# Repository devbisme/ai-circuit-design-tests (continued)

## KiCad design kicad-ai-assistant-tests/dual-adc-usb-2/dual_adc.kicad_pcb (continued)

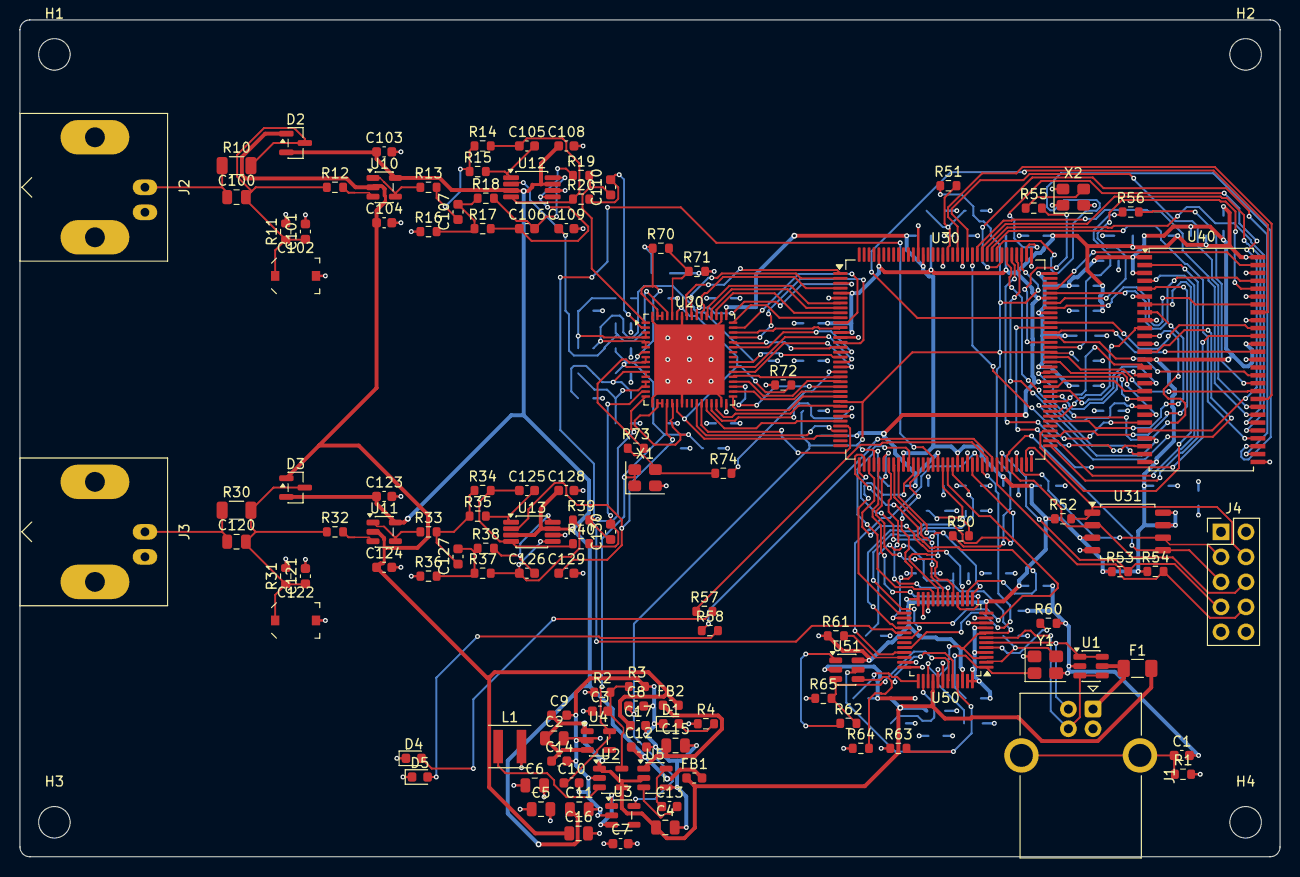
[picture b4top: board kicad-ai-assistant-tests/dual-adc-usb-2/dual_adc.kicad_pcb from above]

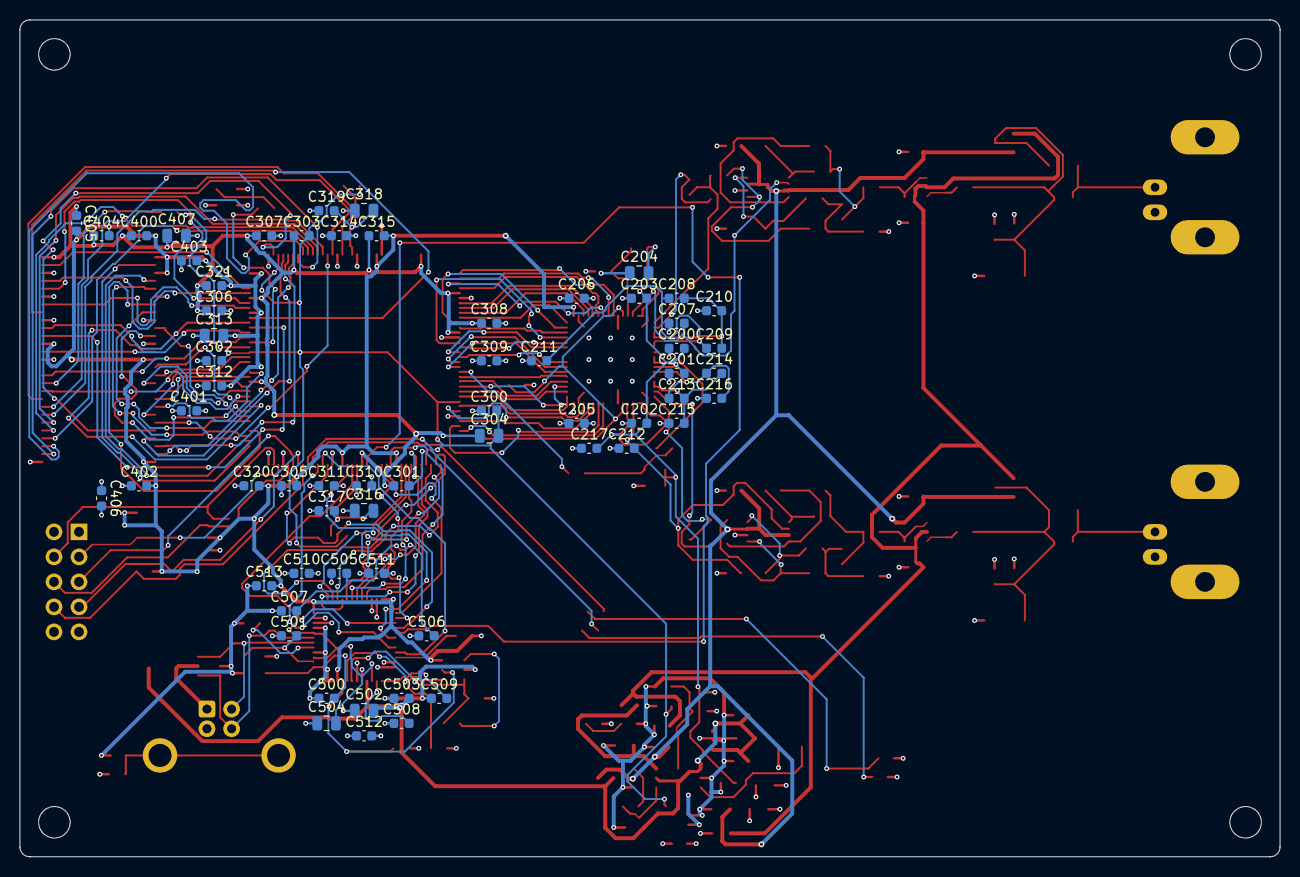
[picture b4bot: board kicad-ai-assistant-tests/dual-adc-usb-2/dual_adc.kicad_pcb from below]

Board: 4 copper layers, 128.0 x 85.0 mm, 182 parts (62 on the bottom side), 160 nets.

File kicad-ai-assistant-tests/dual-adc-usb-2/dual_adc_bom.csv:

Qty,Value,Footprint,References,Description
1,4.7n,Capacitor_SMD:C_0603_1608Metric,C1,shield RF tie (250 V)
6,4.7u,Capacitor_SMD:C_0805_2012Metric,C2 C4 C15 C16 C502 C504,+5V bulk (keep total VBUS C ~10 uF)
1,22p,Capacitor_SMD:C_0603_1608Metric,C3,FB feed-forward
2,22u,Capacitor_SMD:C_0805_2012Metric,C5 C6,buck output
6,1u,Capacitor_SMD:C_0603_1608Metric,C7 C8 C9 C10 C13 C14,LDO in
7,10u,Capacitor_SMD:C_0805_2012Metric,C11 C204 C304 C313 C316 C318 C407,
58,100n,Capacitor_SMD:C_0603_1608Metric,C12 C17 C103 C104 C108 C109 C123 C124 C128 C129 C200 C201 C202 C203 C205 C206 C209 C210 C211 C214 C215 C216 C217 C300 C301 C302 C303 C305 C306 C307 C308 C309 C310 C311 C312 C314 C315 C317 C319 C320 C321 C400 C401 C402 C403 C404 C405 C406 C503 C505 C506 C507 C508 C509 C510 C511 C512 C513,
2,15p C0G 100V,Capacitor_SMD:C_0805_2012Metric,C100 C120,attenuator top comp
2,120p C0G,Capacitor_SMD:C_0603_1608Metric,C101 C121,attenuator bottom comp
2,5-30p,Capacitor_SMD:C_Trimmer_Murata_TZC3,C102 C122,compensation trim (adjust for flat 1 kHz square wave)
4,47p C0G,Capacitor_SMD:C_0603_1608Metric,C105 C106 C125 C126,MFB C2 (signal leg)
2,220p C0G,Capacitor_SMD:C_0603_1608Metric,C107 C127,MFB C1 (differential)
2,470p C0G,Capacitor_SMD:C_0603_1608Metric,C110 C130,"differential RC pole, ~3.4 MHz"
4,2.2u,Capacitor_SMD:C_0603_1608Metric,C207 C208 C212 C213,VCM bypass
2,18p,Capacitor_SMD:C_0603_1608Metric,C500 C501,crystal load
2,green,LED_SMD:LED_0603_1608Metric,D1 D4,power LED
2,BAV99,Package_TO_SOT_SMD:SOT-23,D2 D3,input clamp to analog rails
1,yellow,LED_SMD:LED_0603_1608Metric,D5,status LED 2
1,0.5A hold,Fuse:Fuse_1206_3216Metric,F1,"resettable fuse, 500 mA hold"
2,BLM18PG221,Inductor_SMD:L_0603_1608Metric,FB1 FB2,analog +5 V filter
1,USB-B,Connector_USB:USB_B_OST_USB-B1HSxx_Horizontal,J1,USB 2.0 type-B receptacle
2,BNC,Connector_Coaxial:BNC_Amphenol_B6252HB-NPP3G-50_Horizontal,J2 J3,channel A input (scope-probe compatible)
1,PROG,Connector_PinHeader_2.54mm:PinHeader_2x05_P2.54mm_Vertical,J4,SPI flash programming header (iceprog-style)
1,2.2u XFL4020-222,Inductor_SMD:L_Coilcraft_XxL4020,L1,buck inductor
1,1M,Resistor_SMD:R_0603_1608Metric,R1,shield bleed
1,453k,Resistor_SMD:R_0603_1608Metric,R2,FB top: Vout = 0.6*(1+453k/100k) = 3.32 V
1,100k,Resistor_SMD:R_0603_1608Metric,R3,FB bottom
5,1k,Resistor_SMD:R_0603_1608Metric,R4 R12 R32 R57 R58,
2,909k 0.1%,Resistor_SMD:R_1206_3216Metric,R10 R30,attenuator top
2,100k 0.1%,Resistor_SMD:R_0603_1608Metric,R11 R31,attenuator bottom
4,806,Resistor_SMD:R_0603_1608Metric,R13 R16 R33 R36,MFB R1 (signal leg)
4,768,Resistor_SMD:R_0603_1608Metric,R14 R17 R34 R37,MFB R2 (signal leg)
4,147,Resistor_SMD:R_0603_1608Metric,R15 R18 R35 R38,MFB R3 (signal leg)
4,49.9,Resistor_SMD:R_0603_1608Metric,R19 R20 R39 R40,ADC drive / RC pole
2,100,Resistor_SMD:R_0603_1608Metric,R50 R51,PLL supply filter
9,10k,Resistor_SMD:R_0603_1608Metric,R52 R53 R54 R61 R63 R64 R65 R71 R72,SS_B high at reset -> SPI master boot
3,33,Resistor_SMD:R_0603_1608Metric,R55 R73 R74,
1,22,Resistor_SMD:R_0603_1608Metric,R56,SDRAM clock series term
1,12k 1%,Resistor_SMD:R_0603_1608Metric,R60,FT232H PHY reference
1,2.2k,Resistor_SMD:R_0603_1608Metric,R62,EEPROM DO -> EEDATA
1,20k,Resistor_SMD:R_0603_1608Metric,R70,"MODE = VDD/3: offset binary, DCS on"
1,USBLC6-2SC6,Package_TO_SOT_SMD:SOT-23-6,U1,USB ESD protection
1,TLV62569DBV,Package_TO_SOT_SMD:SOT-23-5,U2,5V->3.3V 2 A buck
1,TLV73312PDBV,Package_TO_SOT_SMD:SOT-23-5,U3,FPGA core 1.2 V LDO
1,LP5907MFX-3.3,Package_TO_SOT_SMD:SOT-23-5,U4,low-noise ADC supply
1,TPS60403DBV,Package_TO_SOT_SMD:SOT-23-5,U5,"inverting charge pump, 60 mA"
2,OPA810IDBVR,Package_TO_SOT_SMD:SOT-23-5,U10 U11,FET-input unity-gain buffer
2,THS4521IDGK,Package_SO:VSSOP-8_3x3mm_P0.65mm,U12 U13,fully-differential ADC driver / 2-pole MFB
1,LTC2290CUP,Package_DFN_QFN:QFN-64-1EP_9x9mm_P0.5mm_EP7.15x7.15mm,U20,dual 12-bit 10 Msps ADC
1,ICE40HX4K-TQ144,Package_QFP:TQFP-144_20x20mm_P0.5mm,U30,"FPGA: capture, SDRAM, USB FIFO"
1,W25Q32JVSSIQ,Package_SO:SOIC-8_5.3x5.3mm_P1.27mm,U31,FPGA configuration flash (32 Mbit)
1,MT48LC16M16A2P-6A,Package_SO:TSOP-II-54_22.2x10.16mm_P0.8mm,U40,256 Mbit SDR SDRAM capture buffer
1,FT232HL,Package_QFP:LQFP-48_7x7mm_P0.5mm,U50,USB 2.0 HS to sync FIFO bridge
1,93LC56BT-I/OT,Package_TO_SOT_SMD:SOT-23-6,U51,FT232H config EEPROM (sets 245 sync FIFO mode)
1,ASE-10.000MHZ,Oscillator:Oscillator_SMD_Abracon_ASE-4Pin_3.2x2.5mm,X1,"10 MHz sample clock (dedicated, low jitter)"
1,ASE-50.000MHZ,Oscillator:Oscillator_SMD_Abracon_ASE-4Pin_3.2x2.5mm,X2,50 MHz system clock
1,12MHz 10pF,Crystal:Crystal_SMD_3225-4Pin_3.2x2.5mm,Y1,FT232H crystal

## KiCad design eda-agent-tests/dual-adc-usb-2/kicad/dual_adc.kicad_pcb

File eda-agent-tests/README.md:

# eda-agent — tests

## Tool under test

[eda-agent](https://github.com/salitronic/eda-agent) is an MCP server with three backends:
Altium Designer (the default and most complete, Windows only), KiCad, and EasyEDA Pro. These
tests used the **KiCad backend**, which exposes 109 tools (`mcp__eda-kicad__*`) for:

- Design creation from a JSON **DesignPlan** written by the LLM: `design_validate_plan`,
  `design_review_plan`, and `kicad_generate_project`, which writes `.kicad_pro`,
  `.kicad_sch` and `.kicad_pcb` from the plan.
- Review: `kicad_full_review` (ERC + DRC + schematic review + schematic/PCB compare),
  `kicad_review_schematic`, `kicad_compare_sch_pcb`.
- Board queries and simple edits (tracks, vias, zones, moves) over KiCad's IPC API.
- Exports (Gerbers, drill, BOM, STEP, renders, …), SPICE, and PCB calculators.

Nearly every KiCad tool needs the KiCad GUI open with its IPC API server enabled. The
`kicad_generate_*` tools write files directly. The autonomous spec-to-board harness
(`autodesign` skill) exists only for Altium and EasyEDA, so it was not installed.
Installation is described in [`setup.md`](setup.md).

The tool is a hybrid (both analyzer and generator), so it is tested in both roles, like
[kicad-mcp-server](../kicad-mcp-server-tests/) and [kicad-mcp-pro](../kicad-mcp-pro-tests/).

- **Version:** eda-agent 0.6.1 (Alpha), commit 8e659a2 (2026-10-07), installed from `main`.
- **Toolset:** full (not `EDA_AGENT_TOOLSET=minimal`), headless (no web dashboard).
- **Model:** Claude Opus 5.5 on a Claude Pro plan, Claude Code v2.1.296 (both runs).
- **Backend:** KiCad 10.0.4 (`~/bin/kicad10-root`, IPC API and bundled Python 3.11),
  Freerouting 2.4.1.

## Runs

| Run | What it tests | Prompts | Outcome | Equiv. API cost | Time |
|---|---|---|---|---|---|
| [`dual-adc-usb-1`](dual-adc-usb-1/) | **Analysis** and fab outputs for an existing design | 1 (`analysis_prompt.txt`) | ERC/DRC 0 errors; 19 ranked issues; Gerbers, BOM, CPL, PNG | $3.43 | ~14 min |
| [`dual-adc-usb-2`](dual-adc-usb-2/) | A **full design**, from requirements to Gerbers | 1, plus 1 for the summary | 7-sheet schematic, routed 4-layer board, ERC and DRC 0 errors | $18.47 | ~1h56m wall clock, ~47 min working |

Each run directory has an `executive_summary.md`; start there. Costs are the equivalent
first-party API price of the tokens used (`claude_cost.txt`), not what the Pro subscription
billed. Run 2's `claude_cost.txt` was generated after the session ended, from that session's
transcripts; it includes the summary prompt. I have not yet validated the findings in either
run myself.

### dual-adc-usb-1: analyzer on an existing design

The input is the KiCad project produced by
[Konnect run 2](../konnect-tests/dual-adc-usb-2/): a 4-layer, 140 × 90 mm dual-channel
12-bit, 10 MS/s ADC board with a USB 2.0 interface (LTC2290 ADC, iCE40HX4K FPGA, SDRAM,
FT2232HL). The KiCad files are unchanged copies of Konnect's (the `.kicad_pcb` md5 matches),
and this run did not modify them. kicad-happy, kicad-mcp-server and kicad-mcp-pro run 1
analyzed the same design.

Prompt (from `claude_transcript.txt`):

```
execute the instructions in analysis_prompt.txt.
```

[`analysis_prompt.txt`](dual-adc-usb-1/analysis_prompt.txt) asks for an architectural,
physical-design and manufacturing review **using eda-agent**, JLCPCB Gerbers, BOM and
pick-and-place files, a dark-gray PCB PNG, and `executive_summary.md`.

This run replaces an earlier run 1 whose prompt didn't name eda-agent; in that one Claude
used only `kicad-cli` and pcbnew Python and made no `eda-kicad` calls. The only change to
the prompt is the words "using eda-agent".

Quick look:

- **Connecting to KiCad:** the dual-adc-usb-2 session's pcbnew held `/tmp/kicad/api.sock`,
  so Claude started a second pcbnew on this board, which took over the socket, and pointed
  the socket back at the other instance afterwards.
- **eda-agent tools used:** `kicad_full_review`; board queries (summary, stackup, fab stats,
  vias, zones, layer usage, trace lengths, diff pairs, net classes, tracks, pads); the
  impedance calculators; `kicad_export_netlist`, `kicad_export_gerbers`, `kicad_export_drill`,
  `kicad_export_bom`, `kicad_export_pos`; and the `kicad_cli` passthrough.
- **Checks:** ERC 0 errors, 203 warnings (201 are missing-library warnings from the
  kicad-cli environment, so ERC's library-mismatch check didn't run). DRC 0 errors,
  0 unconnected, 343 cosmetic or library warnings. Parity: 174 warnings, all `Datasheet`
  field noise or the mounting holes.
- All 34 embedded symbols match the stock KiCad library pin-for-pin. The BAV199DW clamp
  wiring was confirmed against the Diodes datasheet, despite misleading KiCad pin names.
- 19 ranked issues. The most serious:
  - The FPGA's 10 MHz clock runs from the gated analog rail, so there is no clock until USB
    enumerates, and the unpowered ADC may be back-powered by the FPGA.
  - ADC inputs can be driven past absolute maximum by large BNC voltages.
  - Decoupling caps sit 5–22 mm from their pins (14 of 16 FPGA supply pins over 5 mm), and
    the anti-alias caps are 16–18 mm from the ADC.
  - LM27762 feedback resistors (49.9 kΩ) are below the datasheet's 50 kΩ minimum, and its
    unused PGOOD is left open instead of grounded.
  - 40 MB/s is at or above the FT2232H sync-FIFO limit; 16 MB SDRAM gives only ~0.4 s.
- JLCPCB Gerber zip, BOM (blank LCSC column), CPL and a 400 dpi PNG were produced.
- Only the LM27762 and BAV199DW datasheets could be downloaded (FTDI returned 403;
  analog.com timed out). Findings that rest on the FT2232H, LTC2290 and ADA4817 are from the
  model's memory, and the summary marks them.

eda-agent gaps that Claude worked around:

- Every query needs a running KiCad, and the server connects only to `/tmp/kicad/api.sock`.
- `kicad_full_review` truncates ERC and DRC to 200 rows each, so they were rerun in full
  through `kicad_cli`. Its schematic and PCB findings were 53 deliberate single-pin
  no-connect nets, and its decoupling check tests only that caps exist, not their distance.
- `kicad_list_pads` omits component references, so the per-IC geometry (decoupling distances,
  per-net routing) was done with KiCad's bundled pcbnew Python, read-only
  (`reports/scripts/pcb_an.py`).
- The exports aren't fab-ready: Gerbers include all 20 layers, the BOM is one ungrouped row
  per part, and the position file is ASCII in inches. Claude zipped only the fab layers,
  regenerated positions as mm CSV via `kicad_cli`, and converted both to JLC format by
  script. The PNG came from an SVG plotted through `kicad_cli`.

### dual-adc-usb-2: full design

The prompt is [`dual-adc-prompt.txt`](dual-adc-usb-2/dual-adc-prompt.txt). It is identical
to the one used for Konnect run 2, kicad-mcp-server run 2, kicad-happy run 2 and
kicad-mcp-pro run 2.

Prompts, in sequence in one session, with no other user intervention:

```
create the design described in dual-adc-prompt.txt.
```
```
write the executive_summary.md for this run
```

Quick look:

- **Design:** BNC → 1 MΩ compensated ÷11 divider → BAV99 clamp → OPA1656 buffer → THS4521
  FDA → LTC2290; iCE40HX4K with 32 MB SDRAM (0.8 s capture); FT232H sync FIFO; USB-B, bus
  powered (~330 mA estimated). Decisions with options are in
  [`design_decisions.md`](dual-adc-usb-2/design_decisions.md).
- **Schematic:** 7 sheets, 179 parts, 185 nets, ERC 0 errors. The netlist matches the
  DesignPlan net-for-net.
- **PCB:** 125 × 95 mm, 4 layers (In1 GND, In2 +3V3 with a +3V3A island). DRC 0 errors,
  0 unconnected, 0 parity issues, 19 silkscreen warnings. `kicad_full_review` 0 errors.
- **How the server was used:** as a **design tool** for plan validation and review, project
  generation, and the final review and exports. The ~50 kB DesignPlan went through
  `scripts/mcp_call.py`, which calls the tool functions in-process.
- **What it contributed:** the plan validator caught real errors, and the generated board
  had every pad on the right net (725/725), so it became the starting board.
- **Server bugs and gaps:**
  - The generated schematic has no connectivity: its global labels touch no pins (780 ERC
    violations, empty netlist), and multi-unit parts get only unit 1.
  - Symbol and footprint lookup needs a running KiCad, silently falls back to box symbols
    without one, and can't read KiCad 10 `.kicad_symdir` libraries.
  - The generated board is 2-layer with grid placement, FPIDs without library nicknames, and
    no symbol links.
  - No placement, routing, zone or DSN/SES tools on KiCad.
  - `design_review_plan` misidentifies circuits (calls the compensated divider an RC
    high-pass and low-pass).
  - The IPC tools only try `/tmp/kicad/api.sock`; a stale socket blocked them until it was
    relinked.
- **Gaps filled by Claude's own scripts:** a label-based schematic writer, 4-layer
  conversion and placement, plane fanout and DSN, 4 Freerouting runs, a small A* router and
  local re-layout around the LM27762 (all in `scripts/`).
- **Not ready for fab:** the FT232H and LTC2290 support circuits weren't checked against
  datasheets (both downloads failed); input compensation caps are estimates; first-order
  anti-alias filter; no USB pre-enumeration current limit; no SDRAM/FIFO length matching;
  no gateware or host software.

## Layout

```
eda-agent-tests/
├── README.md                   <- this file
├── setup.md                    <- how eda-agent was installed and configured
├── dual-adc-usb-1/             <- run 1: analysis of the Konnect run-2 design
│   ├── executive_summary.md    <- start here
│   ├── analysis_prompt.txt     <- the analysis prompt
│   ├── claude_transcript.txt   <- session transcript (/export)
│   ├── claude_cost.txt         <- token usage and equivalent API cost
│   ├── session_cost.py         <- script that produced claude_cost.txt
│   ├── dual_adc_usb.kicad_pro, .kicad_pcb, .kicad_dru, .kicad_prl, .kicad_sch
│   ├── afe_a, afe_b, adc, fpga, usb, power .kicad_sch
│   ├── reports/                <- drc.json, erc.json, eda_agent_full_review.json, netlist,
│   │                              raw eda-agent BOM/positions, pcb_geometry.txt, scripts/
│   ├── jlcpcb/                 <- Gerber zip, gerbers/, assembly/ (BOM and CPL)
│   └── dual_adc_usb_pcb.png    <- PCB image on a dark-gray background
└── dual-adc-usb-2/             <- run 2: full design from the dual-ADC prompt
    ├── executive_summary.md    <- start here
    ├── README.md               <- run details, eda-agent findings, regeneration steps
    ├── design_decisions.md     <- requirements, derived numbers, decisions with options
    ├── dual-adc-prompt.txt     <- the design prompt
    ├── claude_transcript.txt   <- session transcript (/export)
    ├── claude_cost.txt         <- token usage and equivalent API cost
    ├── session_cost.py         <- script that produced claude_cost.txt
    ├── plan/                   <- DesignPlan (full and compact), review output, no-connects
    ├── eda_agent_raw/          <- the project as kicad_generate_project wrote it
    ├── kicad/                  <- the final KiCad project
    │   ├── dual_adc.kicad_pro, .kicad_sch, .kicad_pcb, .kicad_prl
    │   ├── power, usb, frontend, adc, fpga, memory .kicad_sch
    │   ├── erc.rpt, drc.rpt, dual_adc.net, dual_adc_bom.csv
    │   ├── dual_adc_schematic.pdf, dual_adc_pcb_top.pdf, dual_adc.png (3D render)
    │   └── fab/                <- Gerbers, drill and positions
    ├── route/                  <- placed/prerouted/routed boards, DSN, SES, Freerouting logs
    └── scripts/                <- workarounds for server gaps
        ├── build_plan.py       <- writes the DesignPlan (single source of truth)
        ├── check_pins.py       <- pin coverage check of the plan
        ├── symlib.py           <- reads KiCad 10 .kicad_symdir libraries
        ├── sch_writer.py       <- label-based schematic writer
        ├── mcp_call.py         <- calls eda-agent tools in-process
        ├── build_pcb.py        <- 4 layers, FPIDs, symbol links, placement
        ├── board_sync.py       <- relinks the board to new schematic UUIDs
        ├── route_prep.py       <- plane fanout and DSN for Freerouting
        ├── post_route.py       <- imports the SES
        ├── fix_unrouted.py     <- grid A* router for leftover connections
        ├── surgery_lm27762*.py <- one-off local re-layout around the LM27762
        ├── cleanup_board.py    <- final board cleanup
        ├── patch_project.py    <- net classes (pcbnew Save rewrites .kicad_pro)
        └── check_pcb_nets.py, compare_netlist.py, plot_area.py, plot_draw.py
```

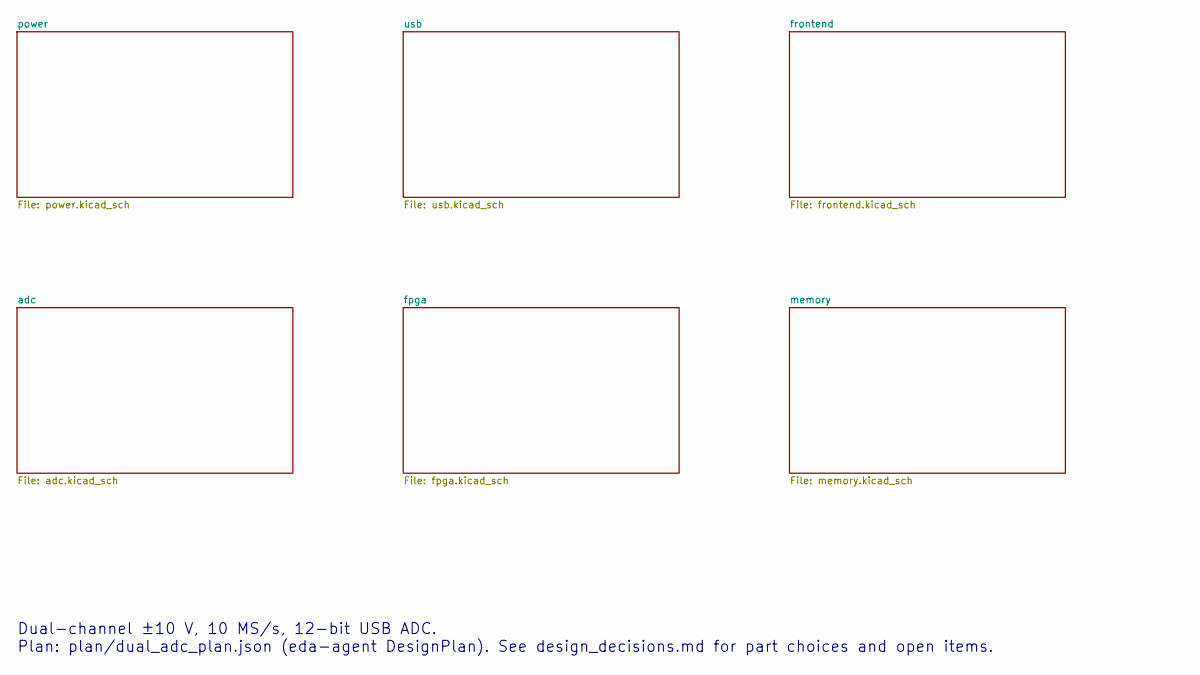
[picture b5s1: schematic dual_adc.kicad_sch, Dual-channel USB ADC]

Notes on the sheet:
Dual-channel ±10 V, 10 MS/s, 12-bit USB ADC. Plan: plan/dual_adc_plan.json (eda-agent DesignPlan). See design_decisions.md for part choices and open items.

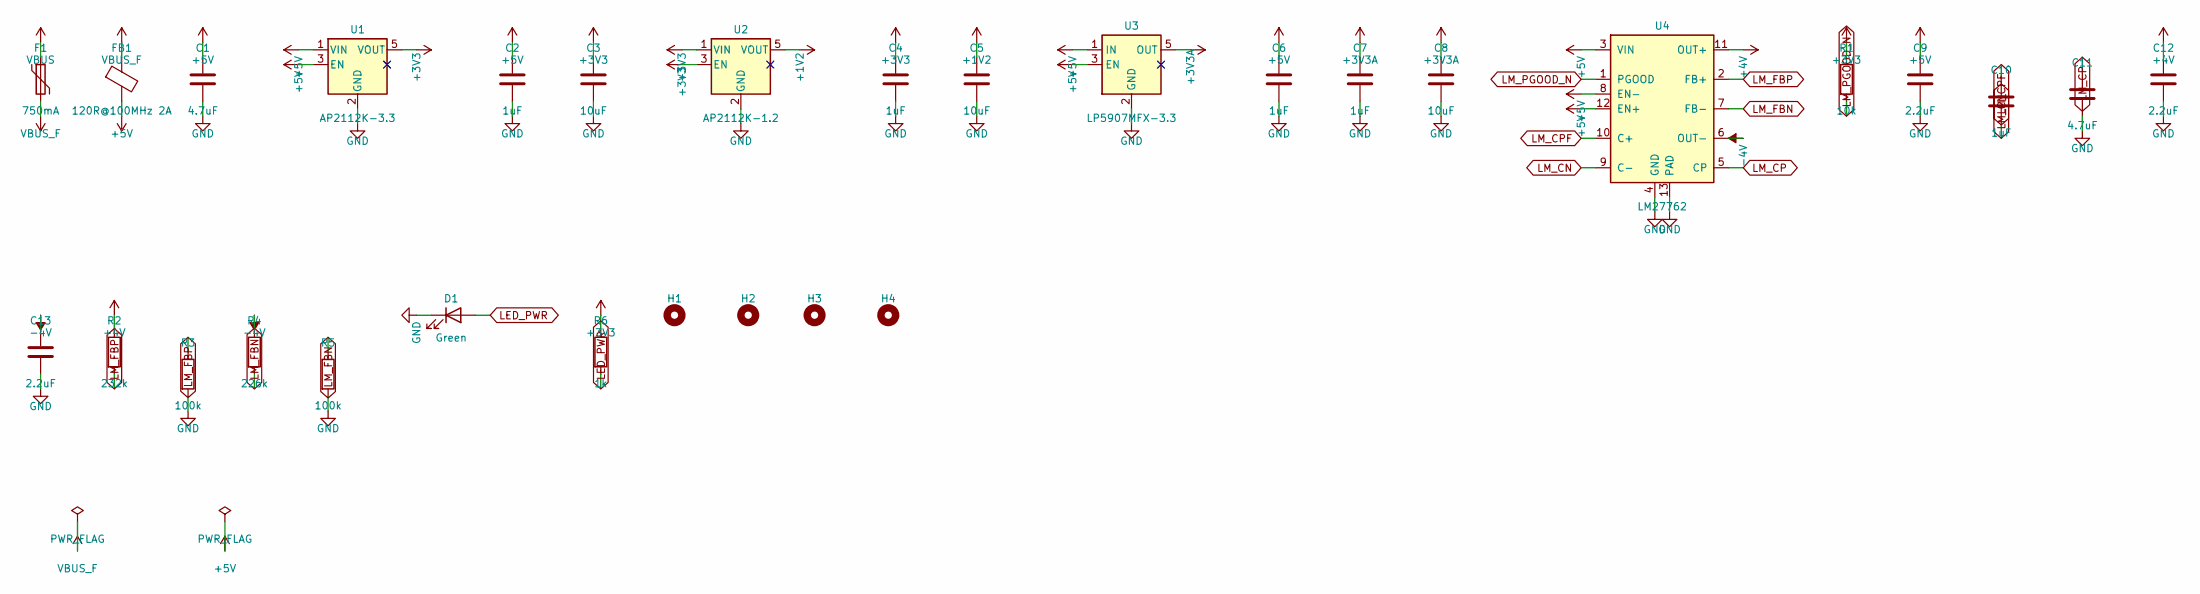
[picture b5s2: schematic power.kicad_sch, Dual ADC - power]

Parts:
C1, C11: 4.7uF; C_0805_2012Metric
C2, C4, C6, C7: 1uF; C_0603_1608Metric
C3, C5, C8: 10uF; C_0805_2012Metric
C9, C12, C13: 2.2uF; C_0805_2012Metric
C10: 1uF; C_0402_1005Metric
D1: Green; LED_0603_1608Metric
F1: 750mA; Fuse_1206_3216Metric; MPN 0ZCJ0050AF2E
FB1: 120R@100MHz 2A; L_0603_1608Metric; MPN BLM18AG601SN1D
H1, H2, H3, H4: MountingHole; MountingHole_3.2mm_M3
R1: 10k; R_0603_1608Metric
R2: 232k; R_0603_1608Metric
R3, R5: 100k; R_0603_1608Metric
R4: 226k; R_0603_1608Metric
R6: 1k; R_0603_1608Metric
U1: AP2112K-3.3; SOT-23-5; MPN AP2112K-3.3TRG1
U2: AP2112K-1.2; SOT-23-5; MPN AP2112K-1.2TRG1
U3: LP5907MFX-3.3; SOT-23-5; MPN LP5907MFX-3.3/NOPB
U4: LM27762; WSON-12-1EP_3x2mm_P0.5mm_EP1x2.65; MPN LM27762DSSR

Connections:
+1V2: C5.1, U2.5 (VOUT); also elsewhere on the board
+3V3: C3.1, C4.1, R1.1, R6.1, U1.5 (VOUT), U2.1 (VIN), U2.3 (EN); also elsewhere on the board
+3V3A: C7.1, C8.1, U3.5 (OUT); also elsewhere on the board
+4V: C12.1, R2.1, U4.11 (OUT+); also elsewhere on the board
+5V: C1.1, C2.1, C6.1, C9.1, FB1.2, U1.1 (VIN), U1.3 (EN), U3.1 (IN), U3.3 (EN), U4.3 (VIN), U4.8 (EN-), U4.12 (EN+)
-4V: C13.1, R4.1, U4.6 (OUT-); also elsewhere on the board
GND: C1.2, C2.2, C3.2, C4.2, C5.2, C6.2, C7.2, C8.2, C9.2, C11.2, C12.2, C13.2, D1.1 (K), R3.2, R5.2, U1.2 (GND), U2.2 (GND), U3.2 (GND), U4.4 (GND), U4.13 (PAD); also elsewhere on the board
LED_PWR: D1.2 (A), R6.2
LM_CN: C10.2, U4.9 (C-)
LM_CP: C11.1, U4.5 (CP)
LM_CPF: C10.1, U4.10 (C+)
LM_FBN: R4.2, R5.1, U4.7 (FB-)
LM_FBP: R2.2, R3.1, U4.2 (FB+)
LM_PGOOD_N: R1.2, U4.1 (PGOOD); also elsewhere on the board
VBUS: F1.1; also elsewhere on the board
VBUS_F: F1.2, FB1.1; also elsewhere on the board

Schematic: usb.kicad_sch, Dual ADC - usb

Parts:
C14: 4.7nF; C_0603_1608Metric
C15, C19, C20, C21, C22, C23, C24, C26, C27, C28: 100nF; C_0603_1608Metric
C16, C17: 27pF; C_0603_1608Metric
C18, C25: 4.7uF; C_0805_2012Metric
FB2: 600R@100MHz; L_0603_1608Metric; MPN BLM18AG601SN1D
J1: USB_B; USB_B_OST_USB-B1HSxx_Horizontal; MPN USB-B1HSW6
R7: 1M; R_0603_1608Metric
R8: 12k; R_0603_1608Metric; Tolerance 1%
R9, R10, R12, R13, R14: 10k; R_0603_1608Metric
R11: 2.2k; R_0603_1608Metric
U5: USBLC6-2SC6; SOT-23-6; MPN USBLC6-2SC6
U6: FT232HL; LQFP-48_7x7mm_P0.5mm; MPN FT232HL-REEL
U7: 93LC56B; SOIC-8_3.9x4.9mm_P1.27mm; MPN 93LC56BT-I/SN
Y1: 12MHz; Crystal_SMD_3225-4Pin_3.2x2.5mm; MPN ABM8-12.000MHZ-B2-T

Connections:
+3V3: C21.1, C22.1, C23.1, C24.1, C25.1, C28.1, FB2.1, R9.1, R10.1, R12.1, R13.1, R14.1, U6.12 (VCCIO), U6.24 (VCCIO), U6.39 (VCCD), U6.40 (VREGIN), U6.46 (VCCIO), U7.8 (VCC); also elsewhere on the board
FT_ACBUS8: U6.32 (ACBUS8); also elsewhere on the board
FT_ACBUS9: U6.33 (ACBUS9); also elsewhere on the board
FT_CLKOUT: U6.29 (ACBUS5); also elsewhere on the board
FT_D0: U6.13 (ADBUS0); also elsewhere on the board
FT_D1: U6.14 (ADBUS1); also elsewhere on the board
FT_D2: U6.15 (ADBUS2); also elsewhere on the board
FT_D3: U6.16 (ADBUS3); also elsewhere on the board
FT_D4: U6.17 (ADBUS4); also elsewhere on the board
FT_D5: U6.18 (ADBUS5); also elsewhere on the board
FT_D6: U6.19 (ADBUS6); also elsewhere on the board
FT_D7: U6.20 (ADBUS7); also elsewhere on the board
FT_EECLK: R13.2, U6.44 (EECLK), U7.2 (SCLK)
FT_EECS: R12.2, U6.45 (EECS), U7.1 (CS)
FT_EEDATA: R11.2, R14.2, U6.43 (EEDATA), U7.3 (DI)
FT_EEDO: R11.1, U7.4 (DO)
FT_OE_N: U6.30 (ACBUS6); also elsewhere on the board
FT_PWRSAV_N: R9.2, U6.31 (ACBUS7)
FT_RD_N: U6.26 (ACBUS2); also elsewhere on the board
FT_REF: R8.1, U6.5 (REF)
FT_RESET_N: R10.2, U6.34 (~RESET)
FT_RXF_N: U6.21 (ACBUS0); also elsewhere on the board
FT_SIWU_N: U6.28 (ACBUS4); also elsewhere on the board
FT_TXE_N: U6.25 (ACBUS1); also elsewhere on the board
FT_VCCA: C26.1, U6.37 (VCCA)
FT_VCORE: C27.1, U6.38 (VCCCORE)
FT_VPHY: C18.1, C19.1, C20.1, FB2.2, U6.3 (VPHY), U6.8 (VPLL)
FT_WR_N: U6.27 (ACBUS3); also elsewhere on the board
FT_XI: C16.1, U6.1 (XCSI), Y1.1
FT_XO: C17.1, U6.2 (XCSO), Y1.3
GND: C14.2, C15.2, C16.2, C17.2, C18.2, C19.2, C20.2, C21.2, C22.2, C23.2, C24.2, C25.2, C26.2, C27.2, C28.2, J1.4 (GND), R7.2, R8.2, U5.2 (GND), U6.4 (AGND), U6.9 (AGND), U6.10 (GND), U6.11 (GND), U6.22 (GND), U6.23 (GND), U6.35 (GND), U6.36 (GND), U6.41 (AGND), U6.42 (TEST), U6.47 (GND), U6.48 (GND), U7.5 (GND), Y1.2 (G), Y1.4 (G); also elsewhere on the board
USB_DM: J1.2 (D-), U5.1 (I/O1), U5.6 (I/O1), U6.6 (DM)
USB_DP: J1.3 (D+), U5.3 (I/O2), U5.4 (I/O2), U6.7 (DP)
USB_SHIELD: C14.1, J1.SH (Shield), R7.1
VBUS: J1.1 (VBUS); also elsewhere on the board
VBUS_F: C15.1, U5.5 (VBUS); also elsewhere on the board

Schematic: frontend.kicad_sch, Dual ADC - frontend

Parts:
C29, C30, C36, C37, C44, C45: 100nF; C_0603_1608Metric
C31, C39: 12pF; C_0603_1608Metric
C32, C40: 2.7pF; C_0603_1608Metric
C33, C41: 22pF; C_0603_1608Metric
C34, C35, C42, C43: 33pF; C_0603_1608Metric
C38, C46: 100pF; C_0603_1608Metric
D2, D3: BAV99; SOT-23; MPN BAV99,215
J2: BNC_A; BNC_Amphenol_B6252HB-NPP3G-50_Horizontal; MPN B6252HB-NPP3G-50
J3: BNC_B; BNC_Amphenol_B6252HB-NPP3G-50_Horizontal; MPN B6252HB-NPP3G-50
R15, R24: 909k; R_0603_1608Metric; Tolerance 0.1%
R16, R25: 90.9k; R_0603_1608Metric; Tolerance 0.1%
R17, R18, R19, R20, R21, R26, R27, R28, R29, R30: 1k; R_0603_1608Metric
R22, R23, R31, R32: 49.9; R_0603_1608Metric
U8: OPA1656ID; SOIC-8_3.9x4.9mm_P1.27mm; MPN OPA1656IDR
U9, U10: THS4521ID; SOIC-8_3.9x4.9mm_P1.27mm; MPN THS4521IDR

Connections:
+3V3A: C36.1, C44.1, U9.3 (V_{S+}), U9.7 (~PD), U10.3 (V_{S+}), U10.7 (~PD); also elsewhere on the board
+4V: C29.1, D2.2 (A), D3.2 (A), U8.8 (V+); also elsewhere on the board
-4V: C30.1, D2.1 (K), D3.1 (K), U8.4 (V-); also elsewhere on the board
AINA_N: C38.2, R23.2; also elsewhere on the board
AINA_P: C38.1, R22.2; also elsewhere on the board
AINB_N: C46.2, R32.2; also elsewhere on the board
AINB_P: C46.1, R31.2; also elsewhere on the board
FDAA_ON: C34.1, R19.1, R23.1, U9.5
FDAA_OP: C35.1, R21.1, R22.1, U9.4
FDAA_SN: C35.2, R20.2, R21.2, U9.1 (-)
FDAA_SP: C34.2, R18.2, R19.2, U9.8 (+)
FDAB_ON: C42.1, R28.1, R32.1, U10.5
FDAB_OP: C43.1, R30.1, R31.1, U10.4
FDAB_SN: C43.2, R29.2, R30.2, U10.1 (-)
FDAB_SP: C42.2, R27.2, R28.2, U10.8 (+)
GND: C29.2, C30.2, C31.2, C33.2, C36.2, C37.2, C39.2, C41.2, C44.2, C45.2, J2.2 (Ext), J3.2 (Ext), R16.2, R20.1, R25.2, R29.1, U9.6 (V_{S-}), U10.6 (V_{S-}); also elsewhere on the board
INA_BUF: R18.1, U8.1, U8.2 (-)
INA_CLAMP: D2.3 (K), R17.2, U8.3 (+)
INA_DIV: C32.2, C33.1, R15.2, R16.1, R17.1
INA_RAW: C31.1, C32.1, J2.1 (In), R15.1
INB_BUF: R27.1, U8.6 (-), U8.7
INB_CLAMP: D3.3 (K), R26.2, U8.5 (+)
INB_DIV: C40.2, C41.1, R24.2, R25.1, R26.1
INB_RAW: C39.1, C40.1, J3.1 (In), R24.1
VCMA: C37.1, U9.2 (V_{OCM}); also elsewhere on the board
VCMB: C45.1, U10.2 (V_{OCM}); also elsewhere on the board

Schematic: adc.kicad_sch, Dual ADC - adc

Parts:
C47, C52, C57, C58, C59, C60, C62, C63, C64: 100nF; C_0603_1608Metric
C48, C51, C53, C56: 2.2uF; C_0805_2012Metric
C49, C50, C54, C55: 1uF; C_0603_1608Metric
C61: 10uF; C_0805_2012Metric
FB3: 600R@100MHz; L_0603_1608Metric; MPN BLM18AG601SN1D
R33: 10k; R_0603_1608Metric
R34: 20k; R_0603_1608Metric
R35, R36, R37: 33; R_0603_1608Metric
RN1, RN2, RN3, RN4, RN5, RN6, RN7: 33; R_Array_Convex_4x0603; MPN CAY16-330J4LF
U11: LTC2290CUP; QFN-64-1EP_9x9mm_P0.5mm_EP7.15x7.15mm; MPN LTC2290CUP#PBF
X1: ASE-10.000MHz; Oscillator_SMD_Abracon_ASE-4Pin_3.2x2.5mm; MPN ASE-10.000MHZ-LC-T

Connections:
+3V3: C62.1, C63.1, U11.32 (OVDD), U11.49 (OVDD); also elsewhere on the board
+3V3A: C57.1, C58.1, C59.1, C60.1, C61.1, FB3.1, R33.1, U11.7 (VDD), U11.10 (VDD), U11.18 (VDD), U11.19 (SENSEB), U11.21 (MUX), U11.62 (SENSEA), U11.63 (VDD); also elsewhere on the board
ADC_CLKA: R35.2, U11.8 (CLKA)
ADC_CLKB: R36.2, U11.9 (CLKB)
ADC_DA0: RN1.8 (R1.2); also elsewhere on the board
ADC_DA0_R: RN1.1 (R1.1), U11.43 (DA0)
ADC_DA1: RN1.7 (R2.2); also elsewhere on the board
ADC_DA1_R: RN1.2 (R2.1), U11.44 (DA1)
ADC_DA2: RN1.6 (R3.2); also elsewhere on the board
ADC_DA2_R: RN1.3 (R3.1), U11.45 (DA2)
ADC_DA3: RN1.5 (R4.2); also elsewhere on the board
ADC_DA3_R: RN1.4 (R4.1), U11.46 (DA3)
ADC_DA4: RN2.8 (R1.2); also elsewhere on the board
ADC_DA4_R: RN2.1 (R1.1), U11.47 (DA4)
ADC_DA5: RN2.7 (R2.2); also elsewhere on the board
ADC_DA5_R: RN2.2 (R2.1), U11.48 (DA5)
ADC_DA6: RN2.6 (R3.2); also elsewhere on the board
ADC_DA6_R: RN2.3 (R3.1), U11.51 (DA6)
ADC_DA7: RN2.5 (R4.2); also elsewhere on the board
ADC_DA7_R: RN2.4 (R4.1), U11.52 (DA7)
ADC_DA8: RN3.8 (R1.2); also elsewhere on the board
ADC_DA8_R: RN3.1 (R1.1), U11.53 (DA8)
ADC_DA9: RN3.7 (R2.2); also elsewhere on the board
ADC_DA9_R: RN3.2 (R2.1), U11.54 (DA9)
ADC_DA10: RN3.6 (R3.2); also elsewhere on the board
ADC_DA10_R: RN3.3 (R3.1), U11.55 (DA10)
ADC_DA11: RN3.5 (R4.2); also elsewhere on the board
ADC_DA11_R: RN3.4 (R4.1), U11.56 (DA11)
ADC_DB0: RN4.7 (R2.2); also elsewhere on the board
ADC_DB0_R: RN4.2 (R2.1), U11.26 (DB0)
ADC_DB1: RN4.6 (R3.2); also elsewhere on the board
ADC_DB1_R: RN4.3 (R3.1), U11.27 (DB1)
ADC_DB2: RN4.5 (R4.2); also elsewhere on the board
ADC_DB2_R: RN4.4 (R4.1), U11.28 (DB2)
ADC_DB3: RN5.8 (R1.2); also elsewhere on the board
ADC_DB3_R: RN5.1 (R1.1), U11.29 (DB3)
ADC_DB4: RN5.7 (R2.2); also elsewhere on the board
ADC_DB4_R: RN5.2 (R2.1), U11.30 (DB4)
ADC_DB5: RN5.6 (R3.2); also elsewhere on the board
ADC_DB5_R: RN5.3 (R3.1), U11.33 (DB5)
ADC_DB6: RN5.5 (R4.2); also elsewhere on the board
ADC_DB6_R: RN5.4 (R4.1), U11.34 (DB6)
ADC_DB7: RN6.8 (R1.2); also elsewhere on the board
ADC_DB7_R: RN6.1 (R1.1), U11.35 (DB7)
ADC_DB8: RN6.7 (R2.2); also elsewhere on the board
ADC_DB8_R: RN6.2 (R2.1), U11.36 (DB8)
ADC_DB9: RN6.6 (R3.2); also elsewhere on the board
ADC_DB9_R: RN6.3 (R3.1), U11.37 (DB9)
ADC_DB10: RN6.5 (R4.2); also elsewhere on the board
ADC_DB10_R: RN6.4 (R4.1), U11.38 (DB10)
ADC_DB11: RN7.8 (R1.2); also elsewhere on the board
ADC_DB11_R: RN7.1 (R1.1), U11.39 (DB11)
ADC_MODE: R33.2, R34.1, U11.60 (MODE)
ADC_OFA: RN4.8 (R1.2); also elsewhere on the board
ADC_OFA_R: RN4.1 (R1.1), U11.57 (OFA)
ADC_OFB: RN7.7 (R2.2); also elsewhere on the board
ADC_OFB_R: RN7.2 (R2.1), U11.40 (OFB)
AINA_N: U11.2 (AINA-); also elsewhere on the board
AINA_P: U11.1 (AINA+); also elsewhere on the board
AINB_N: U11.15 (AINB-); also elsewhere on the board
AINB_P: U11.16 (AINB+); also elsewhere on the board
CLK10: R35.1, R36.1, R37.1, X1.3 (OUT)
FPGA_CLK10: R37.2; also elsewhere on the board
GND: C49.2, C50.2, C51.2, C54.2, C55.2, C56.2, C57.2, C58.2, C59.2, C60.2, C61.2, C62.2, C63.2, C64.2, R34.2, U11.17 (GND), U11.22 (SHDNB), U11.23 (~OEB), U11.31 (OGND), U11.50 (OGND), U11.58 (~OEA), U11.59 (SHDNA), U11.64 (GND), U11.65 (GND), X1.2 (GND); also elsewhere on the board
OSC_VDD: C64.1, FB3.2, X1.1 (EN), X1.4 (Vdd)
REFHA: C47.1, C48.1, C49.1, U11.3 (REFHA), U11.4 (REFHA)
REFHB: C52.1, C53.1, C54.1, U11.13 (REFHB), U11.14 (REFHB)
REFLA: C47.2, C48.2, C50.1, U11.5 (REFLA), U11.6 (REFLA)
REFLB: C52.2, C53.2, C55.1, U11.11 (REFLB), U11.12 (REFLB)
VCMA: C51.1, U11.61 (VCMA); also elsewhere on the board
VCMB: C56.1, U11.20 (VCMB); also elsewhere on the board

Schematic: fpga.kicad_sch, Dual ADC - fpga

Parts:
C65, C66, C67, C68, C70, C71, C72, C73, C74, C75, C76, C77, C78, C79, C82, C84, C85: 100nF; C_0603_1608Metric
C69, C80, C81, C83: 10uF; C_0805_2012Metric
D4, D5: Yellow; LED_0603_1608Metric
J4: PROG; PinHeader_2x04_P2.54mm_Vertical
R38, R39: 100; R_0603_1608Metric
R40, R41, R42, R43, R44: 10k; R_0603_1608Metric
R45, R46: 1k; R_0603_1608Metric
U12: ICE40HX4K-TQ144; TQFP-144_20x20mm_P0.5mm; MPN ICE40HX4K-TQ144
U13: W25Q32JVSS; SOIC-8_5.3x5.3mm_P1.27mm; MPN W25Q32JVSSIQ

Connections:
+1V2: C65.1, C66.1, C67.1, C68.1, C69.1, R38.1, R39.1, U12.27 (VCC), U12.40 (VCC), U12.92 (VCC), U12.111 (VCC); also elsewhere on the board
+3V3: C70.1, C71.1, C72.1, C73.1, C74.1, C75.1, C76.1, C77.1, C78.1, C79.1, C80.1, C85.1, J4.2, R40.1, R41.1, R42.1, R43.1, R44.1, R45.1, R46.1, U12.6 (VCCIO_3), U12.30 (VCCIO_3), U12.46 (VCCIO_2), U12.57 (VCCIO_2), U12.72 (VCC_SPI), U12.89 (VCCIO_1), U12.100 (VCCIO_1), U12.108 (VPP_2V5), U12.123 (VCCIO_0), U12.131 (VCCIO_0), U13.8 (VCC); also elsewhere on the board
ADC_DA0: U12.17 (IOL_12A); also elsewhere on the board
ADC_DA1: U12.16 (IOL_10B); also elsewhere on the board
ADC_DA2: U12.15 (IOL_10A); also elsewhere on the board
ADC_DA3: U12.12 (IOL_8B); also elsewhere on the board
ADC_DA4: U12.11 (IOL_8A); also elsewhere on the board
ADC_DA5: U12.10 (IOL_5B); also elsewhere on the board
ADC_DA6: U12.9 (IOL_5A); also elsewhere on the board
ADC_DA7: U12.8 (IOL_4B); also elsewhere on the board
ADC_DA8: U12.7 (IOL_4A); also elsewhere on the board
ADC_DA9: U12.4 (IOL_3B); also elsewhere on the board
ADC_DA10: U12.3 (IOL_3A); also elsewhere on the board
ADC_DA11: U12.2 (IOL_2B); also elsewhere on the board
ADC_DB0: U12.33 (IOL_25A); also elsewhere on the board
ADC_DB1: U12.32 (IOL_24B); also elsewhere on the board
ADC_DB2: U12.31 (IOL_24A); also elsewhere on the board
ADC_DB3: U12.29 (IOL_23B); also elsewhere on the board
ADC_DB4: U12.28 (IOL_23A); also elsewhere on the board
ADC_DB5: U12.26 (IOL_18B); also elsewhere on the board
ADC_DB6: U12.25 (IOL_18A); also elsewhere on the board
ADC_DB7: U12.24 (IOL_17B); also elsewhere on the board
ADC_DB8: U12.23 (IOL_17A); also elsewhere on the board
ADC_DB9: U12.22 (IOL_14B); also elsewhere on the board
ADC_DB10: U12.20 (IOL_13B_GBIN7); also elsewhere on the board
ADC_DB11: U12.19 (IOL_13A); also elsewhere on the board
ADC_OFA: U12.1 (IOL_2A); also elsewhere on the board
ADC_OFB: U12.18 (IOL_12B); also elsewhere on the board
CDONE: J4.8, R40.2, U12.65 (CDONE)
CFG_SCK: J4.3, U12.70 (IOB_107_SCK), U13.6 (CLK)
CFG_SI: J4.7, U12.68 (IOB_106_SDI), U13.2 (DO/IO_{1})
CFG_SO: J4.5, U12.67 (IOB_105_SDO), U13.5 (DI/IO_{0})
CFG_SS_N: J4.1, R42.2, U12.71 (IOB_108_SS), U13.1 (~CS)
CRESET_N: J4.4, R41.2, U12.66 (~CRESET)
FLASH_HOLD_N: R44.2, U13.7 (~HOLD/~RESET/IO_{3})
FLASH_WP_N: R43.2, U13.3 (~WP/IO_{2})
FPGA_CLK10: U12.21 (IOL_14A_GBIN6); also elsewhere on the board
FT_ACBUS8: U12.61 (IOB_96); also elsewhere on the board
FT_ACBUS9: U12.62 (IOB_102); also elsewhere on the board
FT_CLKOUT: U12.52 (IOB_82_GBIN4); also elsewhere on the board
FT_D0: U12.37 (IOB_56); also elsewhere on the board
FT_D1: U12.38 (IOB_57); also elsewhere on the board
FT_D2: U12.39 (IOB_61); also elsewhere on the board
FT_D3: U12.41 (IOB_63); also elsewhere on the board
FT_D4: U12.42 (IOB_64); also elsewhere on the board
FT_D5: U12.43 (IOB_71); also elsewhere on the board
FT_D6: U12.44 (IOB_72); also elsewhere on the board
FT_D7: U12.45 (IOB_73); also elsewhere on the board
FT_OE_N: U12.56 (IOB_94); also elsewhere on the board
FT_RD_N: U12.49 (IOB_81_GBIN5); also elsewhere on the board
FT_RXF_N: U12.47 (IOB_79); also elsewhere on the board
FT_SIWU_N: U12.60 (IOB_95); also elsewhere on the board
FT_TXE_N: U12.48 (IOB_80); also elsewhere on the board
FT_WR_N: U12.55 (IOB_91); also elsewhere on the board
GND: C65.2, C66.2, C67.2, C68.2, C69.2, C70.2, C71.2, C72.2, C73.2, C74.2, C75.2, C76.2, C77.2, C78.2, C79.2, C80.2, C81.2, C82.2, C83.2, C84.2, C85.2, J4.6, U12.5 (GND), U12.13 (GND), U12.14 (GND), U12.53 (GNDPLL0), U12.59 (GND), U12.69 (GND), U12.86 (GND), U12.103 (GND), U12.127 (GNDPLL1), U12.132 (GND), U12.140 (GND), U13.4 (GND); also elsewhere on the board
LED1_A: D4.2 (A), R45.2
LED1_N: D4.1 (K), U12.63 (IOB_103_CBSEL0)
LED2_A: D5.2 (A), R46.2
LED2_N: D5.1 (K), U12.64 (IOB_104_CBSEL1)
LM_PGOOD_N: U12.101 (IOR_160); also elsewhere on the board
SD_A0: U12.73 (IOR_109); also elsewhere on the board
SD_A1: U12.74 (IOR_110); also elsewhere on the board
SD_A2: U12.75 (IOR_111); also elsewhere on the board
SD_A3: U12.76 (IOR_112); also elsewhere on the board
SD_A4: U12.78 (IOR_114); also elsewhere on the board
SD_A5: U12.79 (IOR_115); also elsewhere on the board
SD_A6: U12.80 (IOR_116); also elsewhere on the board
SD_A7: U12.81 (IOR_117); also elsewhere on the board
SD_A8: U12.82 (IOR_118); also elsewhere on the board
SD_A9: U12.83 (IOR_119); also elsewhere on the board
SD_A10: U12.84 (IOR_120); also elsewhere on the board
SD_A11: U12.85 (IOR_128); also elsewhere on the board
SD_A12: U12.87 (IOR_136); also elsewhere on the board
SD_BA0: U12.88 (IOR_137); also elsewhere on the board
SD_BA1: U12.90 (IOR_138); also elsewhere on the board
SD_CAS_N: U12.94 (IOR_141_GBIN2); also elsewhere on the board
SD_CKE: U12.96 (IOR_146); also elsewhere on the board
SD_CLK: U12.97 (IOR_147); also elsewhere on the board
SD_CS_N: U12.91 (IOR_139); also elsewhere on the board
SD_DQ0: U12.110 (IOT_168); also elsewhere on the board
SD_DQ1: U12.112 (IOT_169); also elsewhere on the board
SD_DQ2: U12.113 (IOT_170); also elsewhere on the board
SD_DQ3: U12.114 (IOT_171); also elsewhere on the board
SD_DQ4: U12.115 (IOT_172); also elsewhere on the board
SD_DQ5: U12.116 (IOT_173); also elsewhere on the board
SD_DQ6: U12.117 (IOT_174); also elsewhere on the board
SD_DQ7: U12.118 (IOT_177); also elsewhere on the board
SD_DQ8: U12.119 (IOT_178); also elsewhere on the board
SD_DQ9: U12.120 (IOT_179); also elsewhere on the board
SD_DQ10: U12.121 (IOT_181); also elsewhere on the board
SD_DQ11: U12.122 (IOT_190); also elsewhere on the board
SD_DQ12: U12.124 (IOT_191); also elsewhere on the board
SD_DQ13: U12.125 (IOT_192); also elsewhere on the board
SD_DQ14: U12.128 (IOT_197_GBIN1); also elsewhere on the board
SD_DQ15: U12.129 (IOT_198_GBIN0); also elsewhere on the board
SD_DQMH: U12.99 (IOR_152); also elsewhere on the board
SD_DQML: U12.98 (IOR_148); also elsewhere on the board
SD_RAS_N: U12.93 (IOR_140_GBIN3); also elsewhere on the board
SD_WE_N: U12.95 (IOR_144); also elsewhere on the board
VCCPLL0: C81.1, C82.1, R38.2, U12.54 (VCCPLL0)
VCCPLL1: C83.1, C84.1, R39.2, U12.126 (VCCPLL1)

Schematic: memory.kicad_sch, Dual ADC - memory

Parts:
C86, C87, C88, C89, C90, C91, C92: 100nF; C_0603_1608Metric
C93: 10uF; C_0805_2012Metric
U14: MT48LC16M16A2TG-6A; TSOP-II-54_22.2x10.16mm_P0.8mm; MPN MT48LC16M16A2P-6A:G

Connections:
+3V3: C86.1, C87.1, C88.1, C89.1, C90.1, C91.1, C92.1, C93.1, U14.1 (VDD), U14.3 (VDDQ), U14.9 (VDDQ), U14.14 (VDD), U14.27 (VDD), U14.43 (VDDQ), U14.49 (VDDQ); also elsewhere on the board
GND: C86.2, C87.2, C88.2, C89.2, C90.2, C91.2, C92.2, C93.2, U14.6 (VSSQ), U14.12 (VSSQ), U14.28 (VSS), U14.41 (VSS), U14.46 (VSSQ), U14.52 (VSSQ), U14.54 (VSS); also elsewhere on the board
SD_A0: U14.23 (A0); also elsewhere on the board
SD_A1: U14.24 (A1); also elsewhere on the board
SD_A2: U14.25 (A2); also elsewhere on the board
SD_A3: U14.26 (A3); also elsewhere on the board
SD_A4: U14.29 (A4); also elsewhere on the board
SD_A5: U14.30 (A5); also elsewhere on the board
SD_A6: U14.31 (A6); also elsewhere on the board
SD_A7: U14.32 (A7); also elsewhere on the board
SD_A8: U14.33 (A8); also elsewhere on the board
SD_A9: U14.34 (A9); also elsewhere on the board
SD_A10: U14.22 (A10); also elsewhere on the board
SD_A11: U14.35 (A11); also elsewhere on the board
SD_A12: U14.36 (A12); also elsewhere on the board
SD_BA0: U14.20 (BA0); also elsewhere on the board
SD_BA1: U14.21 (BA1); also elsewhere on the board
SD_CAS_N: U14.17 (~CAS); also elsewhere on the board
SD_CKE: U14.37 (CKE); also elsewhere on the board
SD_CLK: U14.38 (CLK); also elsewhere on the board
SD_CS_N: U14.19 (~CS); also elsewhere on the board
SD_DQ0: U14.2 (DQ0); also elsewhere on the board
SD_DQ1: U14.4 (DQ1); also elsewhere on the board
SD_DQ2: U14.5 (DQ2); also elsewhere on the board
SD_DQ3: U14.7 (DQ3); also elsewhere on the board
SD_DQ4: U14.8 (DQ4); also elsewhere on the board
SD_DQ5: U14.10 (DQ5); also elsewhere on the board
SD_DQ6: U14.11 (DQ6); also elsewhere on the board
SD_DQ7: U14.13 (DQ7); also elsewhere on the board
SD_DQ8: U14.42 (DQ8); also elsewhere on the board
SD_DQ9: U14.44 (DQ9); also elsewhere on the board
SD_DQ10: U14.45 (DQ10); also elsewhere on the board
SD_DQ11: U14.47 (DQ11); also elsewhere on the board
SD_DQ12: U14.48 (DQ12); also elsewhere on the board
SD_DQ13: U14.50 (DQ13); also elsewhere on the board
SD_DQ14: U14.51 (DQ14); also elsewhere on the board
SD_DQ15: U14.53 (DQ15); also elsewhere on the board
SD_DQMH: U14.39 (DQMH); also elsewhere on the board
SD_DQML: U14.15 (DQML); also elsewhere on the board
SD_RAS_N: U14.18 (~RAS); also elsewhere on the board
SD_WE_N: U14.16 (~WE); also elsewhere on the board
